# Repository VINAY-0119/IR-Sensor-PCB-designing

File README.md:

# IR Sensor Module — KiCad PCB Design

<div align="center">

**Manufacturer:** Vinay Industries &nbsp;|&nbsp; **IC:** LM358 Dual Op-Amp &nbsp;|&nbsp; **Tool:** KiCad EDA &nbsp;|&nbsp; **Version:** 1.0

</div>

---

## 📌 Table of Contents

- [Overview](#-overview)
- [Design Previews](#-design-previews)
- [Circuit Description](#-circuit-description)
- [Bill of Materials](#-bill-of-materials)
- [Connector Pinout](#-connector-pinout--j1)
- [PCB Specifications](#-pcb-specifications)
- [Project Structure](#-project-structure)
- [Getting Started with KiCad](#-getting-started-with-kicad)
- [Gerber Export](#-gerber-export-for-manufacturing)
- [Arduino Integration](#-arduino--microcontroller-integration)
- [Sensitivity Calibration](#-sensitivity-calibration)
- [Important Notes](#-important-notes)
- [License](#-license)

---

## 📖 Overview

This repository contains the complete **KiCad PCB design files** for an **Infrared (IR) Proximity / Obstacle Sensor Module** built around the **LM358 dual operational amplifier**. The circuit uses an IR LED emitter and IR photodiode receiver pair with a comparator stage to detect objects and output a clean **digital signal**.

A blue **trimmer potentiometer (RV1)** allows real-time sensitivity and detection range adjustment without any code changes.

### ✅ Key Features

| Feature | Detail |
|---------|--------|
| Supply Voltage | 5V DC |
| Output Type | Digital (HIGH / LOW) |
| Sensitivity Control | Onboard trimmer potentiometer (RV1) |
| Status Indicator | Onboard LED (D3) lights when object detected |
| MCU Compatibility | Arduino, ESP32, STM32, Raspberry Pi |
| IC | LM358 Dual Op-Amp (DIP-8) |
| PCB Layers | Single-layer (F.Cu) |
| Design Tool | KiCad EDA |

---

## 🖼 Design Previews

### PCB Layout — KiCad PCB Editor

> *Copper trace routing, component placement, silkscreen labels, and board outline as seen in KiCad PCB Editor. Components visible: D1, D2 (IR LEDs), R1–R3 (resistors), RV1 (trimmer), LM358 (DIP-8), D3 (status LED), J1 (3-pin header).*

---

### Schematic — KiCad Schematic Editor

> *Full circuit schematic showing the LM358 comparator, IR emitter/receiver voltage divider, sensitivity trimmer (RV1), and digital output stage with status LED (D3) and 3-pin connector (J1).*

---

### 3D Board Render

> *KiCad 3D render of the assembled PCB. Visible: white IR emitter (D1), black IR photodiode (D2), blue trimmer potentiometer (RV1), LM358 DIP-8 IC, SMD status LED (D3), and 3-pin output header (J1) labeled VCC / GND / DATA.*

---

## ⚡ Circuit Description

```
VCC (+5V)
  │
  ├──► D1 (IR LED Emitter) ──► R1 (100Ω) ──────────────────► GND   [IR Transmission]
  │
  ├──► D2 (IR Photodiode) + R2 (10kΩ divider) ─────────────► LM358 Non-Inverting (+)
  │                                                            [Received IR voltage]
  ├──► RV1 (10kΩ Trimmer) ──────────────────────────────────► LM358 Inverting (−)
  │                                                            [Threshold adjustment]
  │
  └──► LM358 Output ──► R3 (330Ω) ──► D3 (Status LED) ──────► DATA Pin (J1 Pin 3)
```

### How It Works

1. **IR Emitter (D1):** Continuously emits infrared light; current limited by R1 (100Ω).
2. **IR Receiver (D2):** Photodiode paired with R2 (10kΩ) forms a voltage divider. Output voltage rises when reflected IR light is detected from a nearby object.
3. **LM358 Comparator:** The op-amp compares two voltages:
   - **Non-inverting (+):** Photodiode output voltage (rises with reflected IR)
   - **Inverting (−):** Threshold voltage set by trimmer RV1
   - **Output:** HIGH when object detected, LOW when no object
4. **Output Stage:** When output is HIGH, current flows through R3 (330Ω) and lights status LED D3. The DATA pin simultaneously outputs HIGH for the MCU to read.
5. **Sensitivity Adjust (RV1):** Rotating the blue trimmer adjusts the comparator threshold and detection range.

---

## 🧾 Bill of Materials

| Ref | Component | Value | Package | Description |
|-----|-----------|-------|---------|-------------|
| D1 | IR LED Emitter | — | 5mm Through-hole | Infrared emitter (white body) |
| D2 | IR Photodiode | — | 5mm Through-hole | Infrared receiver (black body) |
| D3 | Status LED | — | SMD | Object detection indicator |
| R1 | Resistor | 100Ω | Through-hole | IR LED current limiter |
| R2 | Resistor | 10kΩ | Through-hole | Photodiode voltage divider |
| R3 | Resistor | 330Ω | Through-hole | Output LED current limiter |
| RV1 | Trimmer Pot | 10kΩ | Top-adjust blue | Sensitivity / threshold adjustment |
| U1 | LM358 | — | DIP-8 | Dual operational amplifier |
| J1 | Pin Header | 3-pin | 2.54mm pitch | VCC / GND / DATA output connector |

---

## 📌 Connector Pinout — J1

```
      J1 — 3-Pin Header (2.54mm pitch)
  ┌─────┬──────────┬────────────────────────────────────┐
  │ Pin │  Label   │ Description                        │
  ├─────┼──────────┼────────────────────────────────────┤
  │  1  │   VCC    │ Power supply input (+5V DC)        │
  │  2  │   GND    │ Ground                             │
  │  3  │  DATA    │ Digital output (HIGH = detected)   │
  └─────┴──────────┴────────────────────────────────────┘
```

> ⚠️ **Always verify polarity before connecting power. Reverse polarity may damage the IC.**

---

## 📐 PCB Specifications

| Parameter | Value |
|-----------|-------|
| Board Dimensions | ~75mm × 28mm |
| PCB Layers | 1 (Single-sided — F.Cu) |
| Surface Finish | HASL |
| PCB Thickness | 1.6mm |
| Min Track Width | 0.25mm |
| Min Clearance | 0.2mm |
| Silkscreen | Front side (labels + Vinay Industries branding) |
| IC Package | DIP-8 through-hole |
| LED Package | 5mm through-hole (D1, D2) + SMD (D3) |

---

## 📁 Project Structure

```
IR-Sensor-Module/
├── README.md                        ← This file
├── images/
│   ├── pcb_layout.png               ← PCB layout screenshot
│   ├── schematic.png                ← Schematic screenshot
│   └── 3d_render.png                ← 3D board render
├── IR_Sensor.kicad_pro              ← KiCad project file
├── IR_Sensor.kicad_sch              ← Schematic
├── IR_Sensor.kicad_pcb              ← PCB layout
├── fp-lib-table                     ← Footprint library table
├── sym-lib-table                    ← Symbol library table
├── gerbers/                         ← Gerber files for manufacturing
│   ├── IR_Sensor-F_Cu.gbr
│   ├── IR_Sensor-F_Silkscreen.gbr
│   ├── IR_Sensor-F_Mask.gbr
│   ├── IR_Sensor-Edge_Cuts.gbr
│   └── IR_Sensor-PTH.drl
└── bom/
    └── BOM.csv
```

---

## 🚀 Getting Started with KiCad

**Prerequisites:** [KiCad 7.x or later](https://www.kicad.org/download/)

```bash
# Clone the repository
git clone https://github.com/vinay-industries/ir-sensor-module.git
cd ir-sensor-module
```

In KiCad:
- **File → Open Project** → select `IR_Sensor.kicad_pro`
- Open **Schematic Editor** to view/edit the circuit diagram
- Open **PCB Editor** to view/edit the board layout
- In PCB Editor → **View → 3D Viewer** to inspect the 3D model

---

## 🏭 Gerber Export for Manufacturing

In KiCad PCB Editor:

```
File → Fabrication Outputs → Gerbers (.gbr)
```

| Layer | Purpose |
|-------|---------|
| F.Cu | Front copper traces |
| F.Silkscreen | Component labels |
| F.Mask | Solder mask |
| Edge.Cuts | Board outline |
| PTH Drill | Drill holes |

Zip the `/gerbers` folder and upload to your PCB manufacturer:
- [JLCPCB](https://jlcpcb.com) — Recommended for prototypes
- [PCBWay](https://www.pcbway.com)
- [OSH Park](https://oshpark.com)

---

## 🔌 Arduino / Microcontroller Integration

### Wiring

```
IR Sensor Module          Arduino Uno
─────────────────         ───────────
     VCC     ──────────►  5V
     GND     ──────────►  GND
     DATA    ──────────►  D7
```

### Example Sketch

```cpp
#define IR_SENSOR_PIN 7

void setup() {
  pinMode(IR_SENSOR_PIN, INPUT);
  Serial.begin(9600);
  Serial.println("IR Sensor Module Ready — Vinay Industries");
}

void loop() {
  int state = digitalRead(IR_SENSOR_PIN);

  if (state == HIGH) {
    Serial.println("Object Detected!");
  } else {
    Serial.println("No Object.");
  }

  delay(100);
}
```

---

## 🎛 Sensitivity Calibration

1. Power the module with **+5V DC** via J1 (VCC and GND pins).
2. Place a target object at your desired detection distance.
3. Using a small flathead screwdriver, slowly rotate the **blue trimmer (RV1)**:
   - **Clockwise** → Increases sensitivity (longer detection range)
   - **Counter-clockwise** → Decreases sensitivity (shorter range)
4. Stop when **Status LED D3 just turns ON** — calibration is complete.

> 💡 **Tip:** Recalibrate when changing target surface color or ambient lighting conditions.

---

## ⚠️ Important Notes

- **Digital output only** — no analog voltage is provided on the DATA pin.
- **Detection range:** Typically 2 cm – 30 cm depending on surface reflectivity.
- **Dark/black surfaces** absorb IR and significantly reduce effective range.
- **Avoid direct sunlight** — ambient IR can cause false positive detections.
- **LM358 output** is not rail-to-rail; LOW output may not reach exactly 0V.
- **Verify connector polarity** (VCC/GND/DATA) before applying power.

---

## 📜 License

This project is licensed under the **MIT License** — see the [LICENSE](LICENSE) file for details.
Free to use, modify, and manufacture for personal or commercial purposes with attribution.

---

<div align="center">

**Vinay Industries** — KiCad PCB Design | Embedded Electronics

*Designed with ❤️ using [KiCad EDA](https://www.kicad.org)*

<div align="center">

**Manufacturer:** Vinay Industries &nbsp;|&nbsp; **IC:** LM358 Dual Op-Amp &nbsp;|&nbsp; **Tool:** KiCad EDA &nbsp;|&nbsp; **Version:** 1.0

</div>

---

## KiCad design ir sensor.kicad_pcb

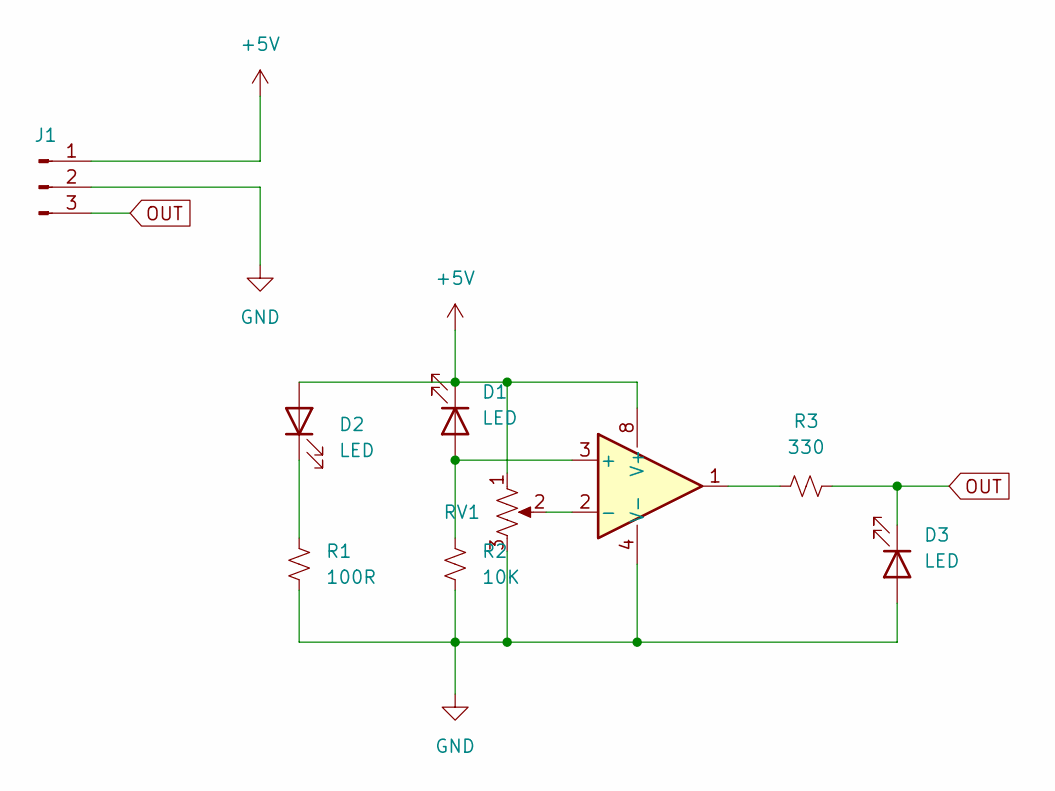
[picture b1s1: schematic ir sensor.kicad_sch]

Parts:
D1: LED; LED_D5.0mm_Horizontal_O1.27mm_Z3.0mm_Clear
D2: LED; LED_D5.0mm_Horizontal_O1.27mm_Z3.0mm_IRBlack
D3: LED; LED_1206_3216Metric_Pad1.42x1.75mm_HandSolder
J1: Conn_01x03_Pin; PinHeader_1x03_P1.00mm_Horizontal
R1: 100R; R_0402_1005Metric_Pad0.72x0.64mm_HandSolder
R2: 10K; R_0402_1005Metric_Pad0.72x0.64mm_HandSolder
R3: 330; R_0402_1005Metric_Pad0.72x0.64mm_HandSolder
RV1: 10K; Potentiometer_Bourns_3266Y_Vertical
U1: LM358; DIP-8_W7.62mm

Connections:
+5V: D1.1 (K), D2.2 (A), J1.1, RV1.1, U1.8 (V+)
GND: D3.2 (A), J1.2, R1.2, R2.2, RV1.3, U1.4 (V-)
unnamed: D1.2 (A), R2.1, U1.3 (+)
unnamed: D2.1 (K), R1.1
unnamed: R3.1, U1.1
unnamed: RV1.2, U1.2 (-)
OUT: D3.1 (K), J1.3, R3.2

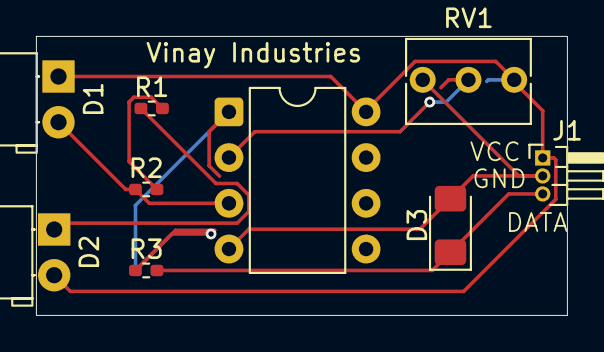
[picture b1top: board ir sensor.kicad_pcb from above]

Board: 2 copper layers, 29.5 x 15.5 mm, 9 parts (0 on the bottom side), 7 nets.

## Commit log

2026-03-22 Clean up README by removing sections
    Removed Table of Contents and several sections from the README.
2026-03-22 Fix heading for IR Sensor Module in README
    Removed incorrect heading for IR Sensor Module.

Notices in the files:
README.md:
License: MIT
